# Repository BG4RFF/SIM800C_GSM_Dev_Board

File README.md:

# SIM800C_GSM_Dev_Board
SIM800C GSM Module Development Board with power and processor (ESP8266).

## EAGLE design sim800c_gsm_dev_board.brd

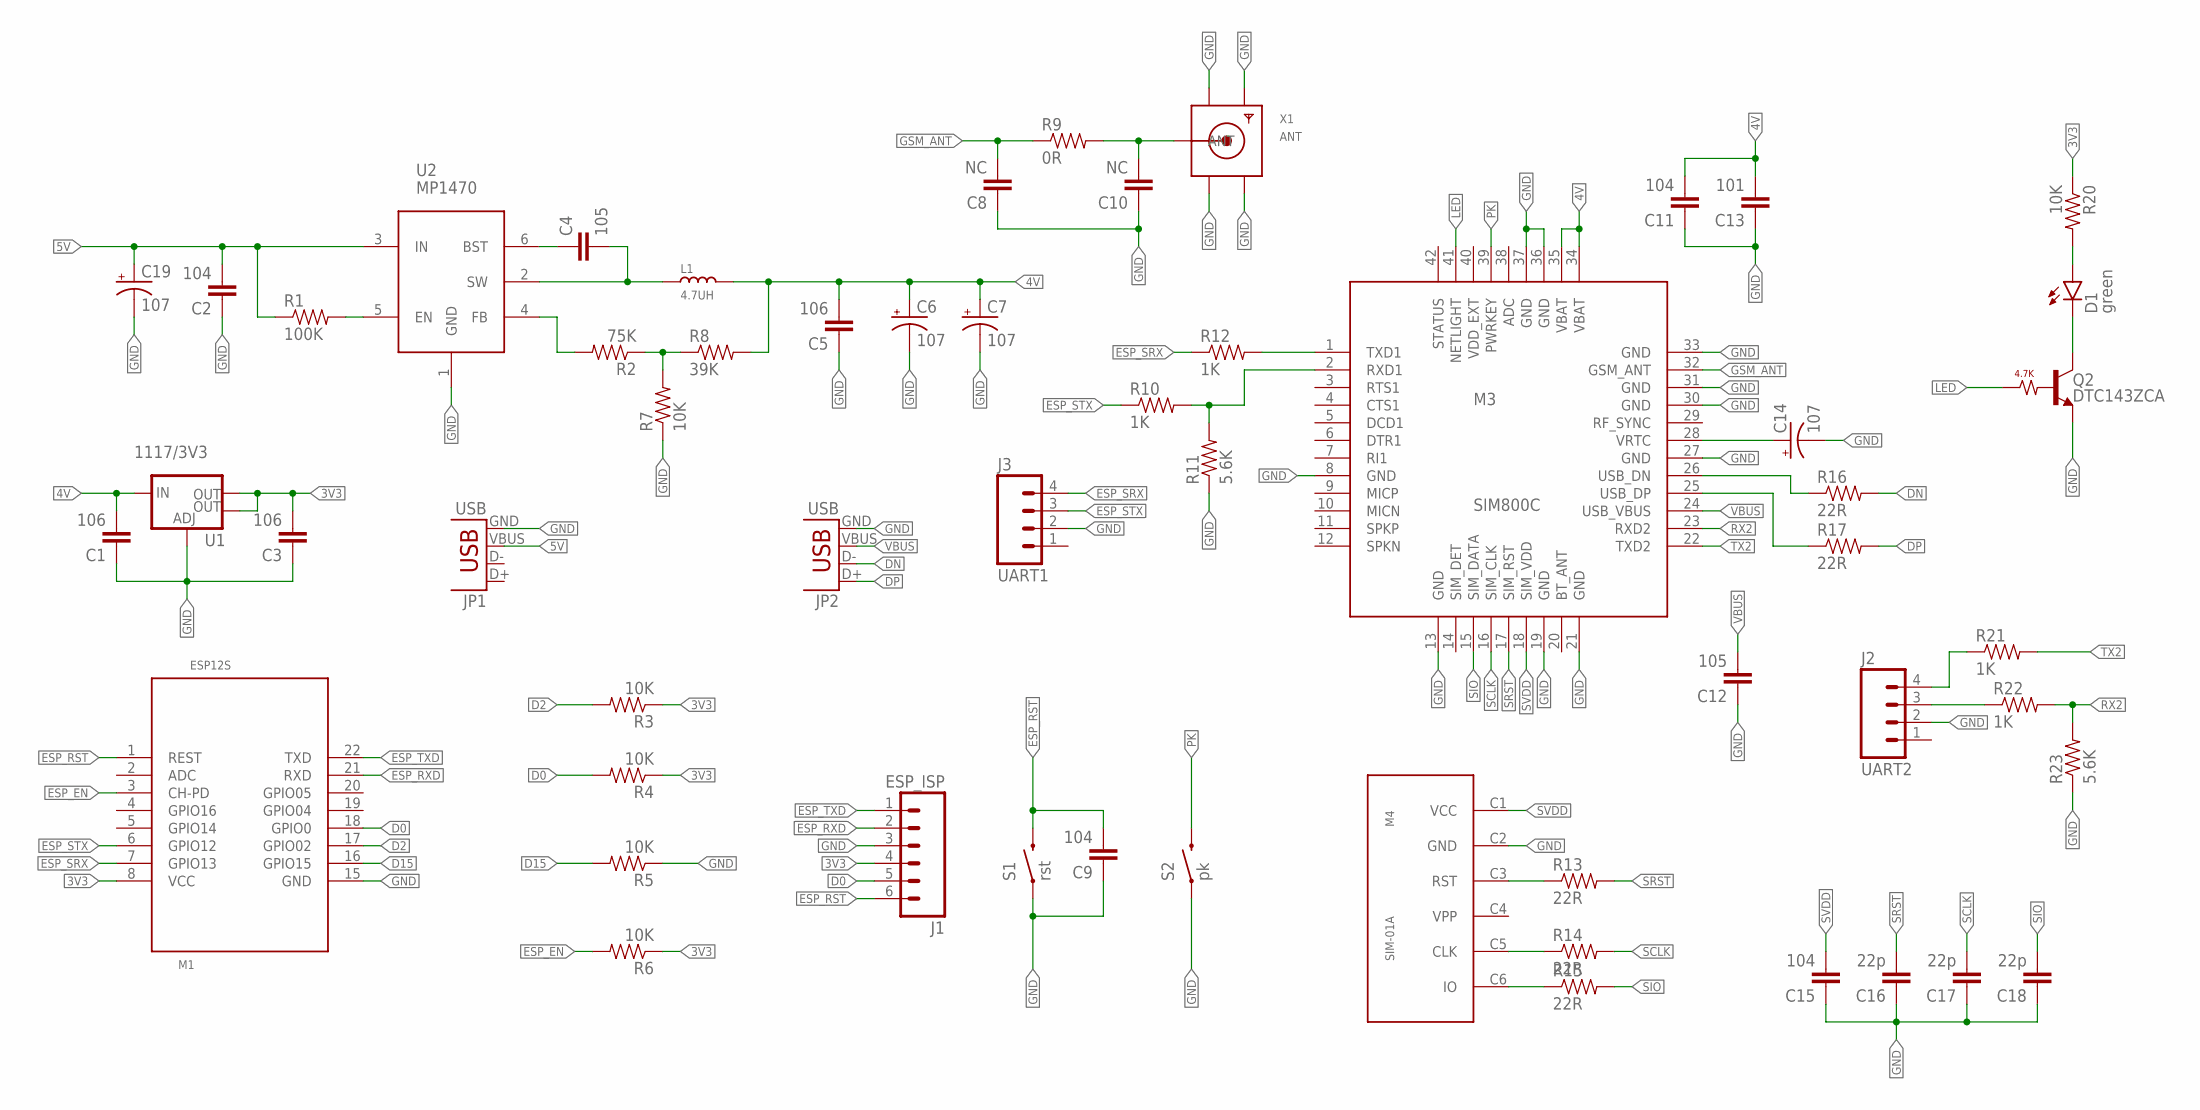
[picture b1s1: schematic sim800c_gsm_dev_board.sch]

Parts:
C1, C3, C5: 106; 0603-CAP
C2: 104; 0603-CAP
C4, C12: 105; 0603-CAP
C6, C7, C14, C19: 107; EIA3528
C8, C10: NC; C0402
C9, C11, C15: 104; C0402
C13: 101; C0402
C16, C17, C18: 22p; C0402
D1: green; LED-0603-SEEED
J1: ESP_ISP; 1X06_NO_SILK
J2: UART2; 1X04_NO_SILK_ALL_ROUND
J3: UART1; 1X04_NO_SILK_ALL_ROUND
JP1, JP2: USB; MICROUSB-U-F-M5DD-Y-1
L1: 4.7UH; SMD-2P-5.0X5.0X2.0MM
M1: ESP12S; LGA22-2.0-24X16MM-SIMPLE
M3: SIM800C
M4: SIM-01A
Q2: DTC143ZCA; SOT23-3
R1: 100K; R0402
R2: 75K; R0402
R3, R4, R5, R6, R7, R20: 10K; R0402
R8: 39K; R0402
R9: 0R; R0402
R10, R12, R21, R22: 1K; R0402
R11, R23: 5.6K; R0402
R13, R14, R15, R16, R17: 22R; R0402
S1: rst; TACTILE_SWITCH_TALL
S2: pk; TACTILE_SWITCH_TALL
U1: 1117/3V3; SOT223
U2: MP1470; SOT23-6
X1: ANT; SMA90_DIP

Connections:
3V3: C3.2, J1.4, M1.8 (VCC), R3.1, R4.1, R6.1, R20.1, U1.2 (OUT), U1.4 (OUT)
4V: C1.2, C5.2, C6.A (+), C7.A (+), C11.2, C13.2, L1.2, M3.34 (VBAT), M3.35 (VBAT), R8.2, U1.3 (IN)
5V: C2.2, C19.A (+), JP1.VBUS, R1.1, U2.3 (IN)
D0: J1.5, M1.18 (GPIO0), R4.2
D2: M1.17 (GPIO02), R3.2
D15: M1.16 (GPIO15), R5.2
DN: JP2.D-, R16.2
DP: JP2.D+, R17.2
ESP_EN: M1.3 (CH-PD), R6.2
ESP_RST: C9.2, J1.6, M1.1 (REST), S1.B2 (2)
ESP_RXD: J1.2, M1.21 (RXD)
ESP_SRX: J3.4, M1.7 (GPIO13), R12.1
ESP_STX: J3.3, M1.6 (GPIO12), R10.1
ESP_TXD: J1.1, M1.22 (TXD)
GND: C1.1, C2.1, C3.1, C5.1, C6.C (-), C7.C (-), C8.1, C9.1, C10.1, C11.1, C12.1, C13.1, C14.C (-), C15.1, C16.1, C17.1, C18.1, C19.C (-), J1.3, J2.2, J3.2, JP1.GND, JP2.GND, M1.15 (GND), M3.8 (GND), M3.13 (GND), M3.19 (GND), M3.21 (GND), M3.27 (GND), M3.30 (GND), M3.31 (GND), M3.33 (GND), M3.36 (GND), M3.37 (GND), M4.C2 (GND), Q2.2 (E), R5.1, R7.1, R11.1, R23.1, S1.A2 (1), S2.A2 (1), U1.1 (ADJ), U2.1 (GND), X1.GND1, X1.GND2, X1.GND3, X1.GND4
GSM_ANT: C8.2, M3.32 (GSM_ANT), R9.1
LED: M3.41 (NETLIGHT), Q2.1 (B)
unnamed: J2.4, R21.1
unnamed: R1.2, U2.5 (EN)
unnamed: M4.C3 (RST), R13.1
unnamed: C4.1, U2.6 (BST)
unnamed: M4.C5 (CLK), R14.1
unnamed: M4.C6 (IO), R15.1
unnamed: R2.2, U2.4 (FB)
unnamed: R2.1, R7.2, R8.1
unnamed: C10.2, R9.2, X1.ANTENNA (ANT)
unnamed: M3.1 (TXD1), R12.2
unnamed: M3.2 (RXD1), R10.2, R11.2
unnamed: D1.- (C), Q2.3 (C)
unnamed: D1.+ (A), R20.2
unnamed: J2.3, R22.1
unnamed: M3.25 (USB_DP), R17.1
unnamed: M3.26 (USB_DN), R16.1
unnamed: C14.A (+), M3.28 (VRTC)
PK: M3.39 (PWRKEY), S2.B2 (2)
RX2: M3.23 (RXD2), R22.2, R23.2
SCLK: C17.2, M3.16 (SIM_CLK), R14.2
SIO: C18.2, M3.15 (SIM_DATA), R15.2
SRST: C16.2, M3.17 (SIM_RST), R13.2
SVDD: C15.2, M3.18 (SIM_VDD), M4.C1 (VCC)
SW: C4.2, L1.1, U2.2 (SW)
TX2: M3.22 (TXD2), R21.2
VBUS: C12.2, JP2.VBUS, M3.24 (USB_VBUS)

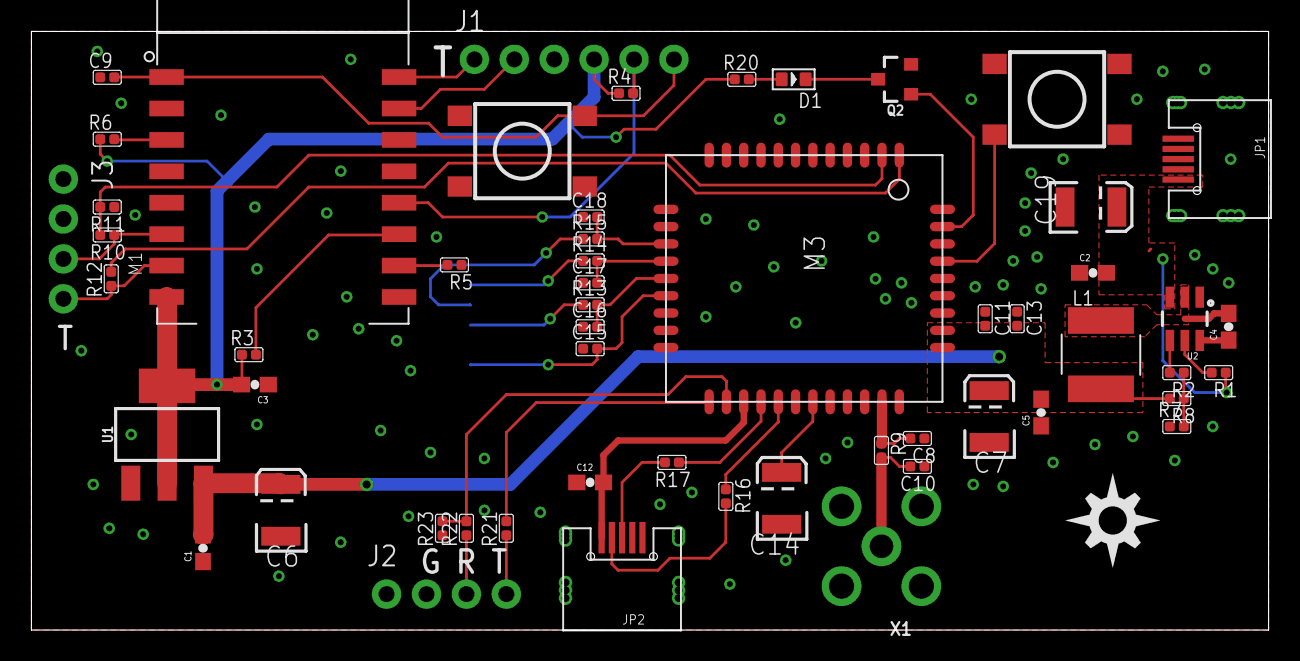
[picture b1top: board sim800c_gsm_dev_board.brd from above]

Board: 2 copper layers, 78.7 x 38.1 mm, 57 parts (1 on the bottom side), 43 nets.

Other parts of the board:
U$1: DIYNOVA_LOGO

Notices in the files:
parts and their libraries:
SparkFun-Connectors: Licensing: Creative Commons ShareAlike 4.0 International - https://creativecommons.org/licenses/by-sa/4.0
